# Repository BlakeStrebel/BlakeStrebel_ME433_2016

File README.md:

Blake Strebel
4/1/2016
Repository containing work for ME433 Advanced Mechatronics course, Northwestern Universty.

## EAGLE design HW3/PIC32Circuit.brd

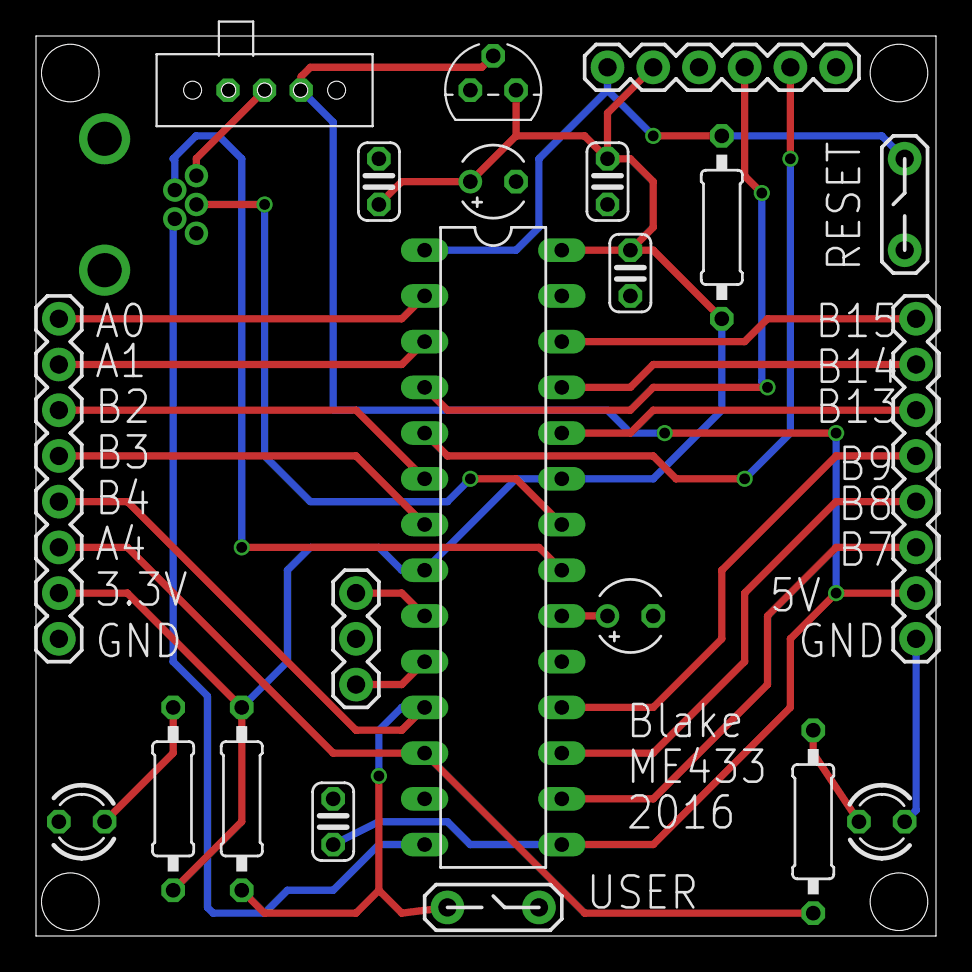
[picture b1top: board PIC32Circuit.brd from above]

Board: 2 copper layers, 50.0 x 50.0 mm, 22 parts (0 on the bottom side), 27 nets.

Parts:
C1, C2, C3, C4: 0.1uF; C025-024X044
C5, C6: 10uF; TT2D4
J1: USB-MB-H
J4, J5: 1X08_ROUND
LED1, LED3: LED3MM
PICKIT3: 1X06
R1, R2: 10k; 0207/10
R4, R5: 330; 0207/10
RES: 8MHz; 1X03
RESET: PUSHBUTTON
U$1: PIC32MX250F128B; DIL28-3
U$2: SLIDERSWITCH
U$3: MCP1702; TO92
USER: PUSHBUTTON

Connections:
3V3: C2.2, C3.1, C4.1, C5.+, J5.7, PICKIT3.2, R1.1, R2.2, R4.1, U$1.8, U$1.23, U$1.28, U$3.3
5V: C1.1, J4.7, U$1.15, U$2.P$3, U$3.2
A0: J5.1, U$1.2
A1: J5.2, U$1.3
A4: J5.6, R5.1, U$1.12
B2: J5.3, U$1.6
B3: J5.4, U$1.7
B4: J5.5, R2.1, U$1.11, USER.1
B7: J4.6, U$1.16
B8: J4.5, U$1.17
B9: J4.4, U$1.18
B13: J4.3, U$1.24
B14: J4.2, U$1.25
B15: J4.1, U$1.26
D+: J1.D+, U$1.22
D-: J1.D-, U$1.21
GND: C1.2, C2.1, C3.2, C4.2, C5.-, C6.-, J1.GND, J4.8, J5.8, LED1.K, LED3.K, PICKIT3.3, RES.2, RESET.1, U$1.13, U$1.19, U$1.27, U$3.1, USER.3
ID: J1.ID, U$1.14
MCLR: PICKIT3.1, R1.2, RESET.3, U$1.1
unnamed: LED1.A, R4.2
unnamed: C6.+, U$1.20
unnamed: J1.VBUS, U$2.P$2
unnamed: LED3.A, R5.2
OSC1: RES.1, U$1.9
OSC2: RES.3, U$1.10
PGC: PICKIT3.5, U$1.5
PGD: PICKIT3.4, U$1.4

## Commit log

2016-04-01 :space_invader: Added .gitattributes & .gitignore files
2016-04-01 Test
2016-04-04 Sketch of circuit diagram
2016-04-04 Voltage Regulator without Capacitors
2016-04-04 PIC32 Circuit
2016-04-04 Create HW1 Project
2016-04-05 Template
2016-04-05 Configurations
2016-04-05 LED turns on
2016-04-05 Core timer testing
2016-04-05 HW1 Final Code
2016-04-08 Eagle set-up
2016-04-08 Library
2016-04-08 Library Update
2016-04-08 EAGLE Layout
2016-04-09 Board Layout
2016-04-09 board updates
2016-04-14 Ready to be checked before order
2016-04-24 SPI/DAC
2016-04-26 I2C + Expander
2016-05-10 Hello LCD
2016-05-12 IMU + LCD
2016-05-24 Android Hello World
2016-05-29 Wheel
2016-06-04 HW8 CDC
2016-06-04 HW12
2016-06-05 HW13
2016-06-05 Use User LED
2016-06-05 HW14 Camera + CDC
2016-06-05 Send COM to PIC
2016-06-06 HW15
2016-06-07 Completed Robot
2016-06-09 HW11: Whale CAD
    fancy box
2016-06-09 HW7 builds
2016-06-09 emulating
